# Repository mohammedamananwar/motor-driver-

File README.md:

# PCB 3D View

This is a 3D view of the designed PCB board.  
It contains various components such as:
- Terminal blocks for external connections (green connectors)
- IC (integrated circuit) mounted in DIP package
- Voltage regulator or transistor in TO-220 package with a heatsink
- A resistor
- A push button (yellow colored)
- Other essential electronic components required for circuit operation.

> **Note:**  
> There is a warning:  
> "**Board outline is missing or malformed. Run DRC for a full analysis.**"  
> Make sure to correct the board outline in your PCB design tool.

---

## 3D View Image:

---

## Observations:
- Proper placement of components is visible.
- Sufficient spacing for terminal connections.
- The IC and voltage regulator are well-positioned.
- Board outline needs to be corrected for final production.

## Suggestions:
- Fix the board outline error.
- Verify clearances and perform a Design Rule Check (DRC).
- Add labels for terminals (optional but helpful).

---

_Rendering Time:_ **16.663 seconds**

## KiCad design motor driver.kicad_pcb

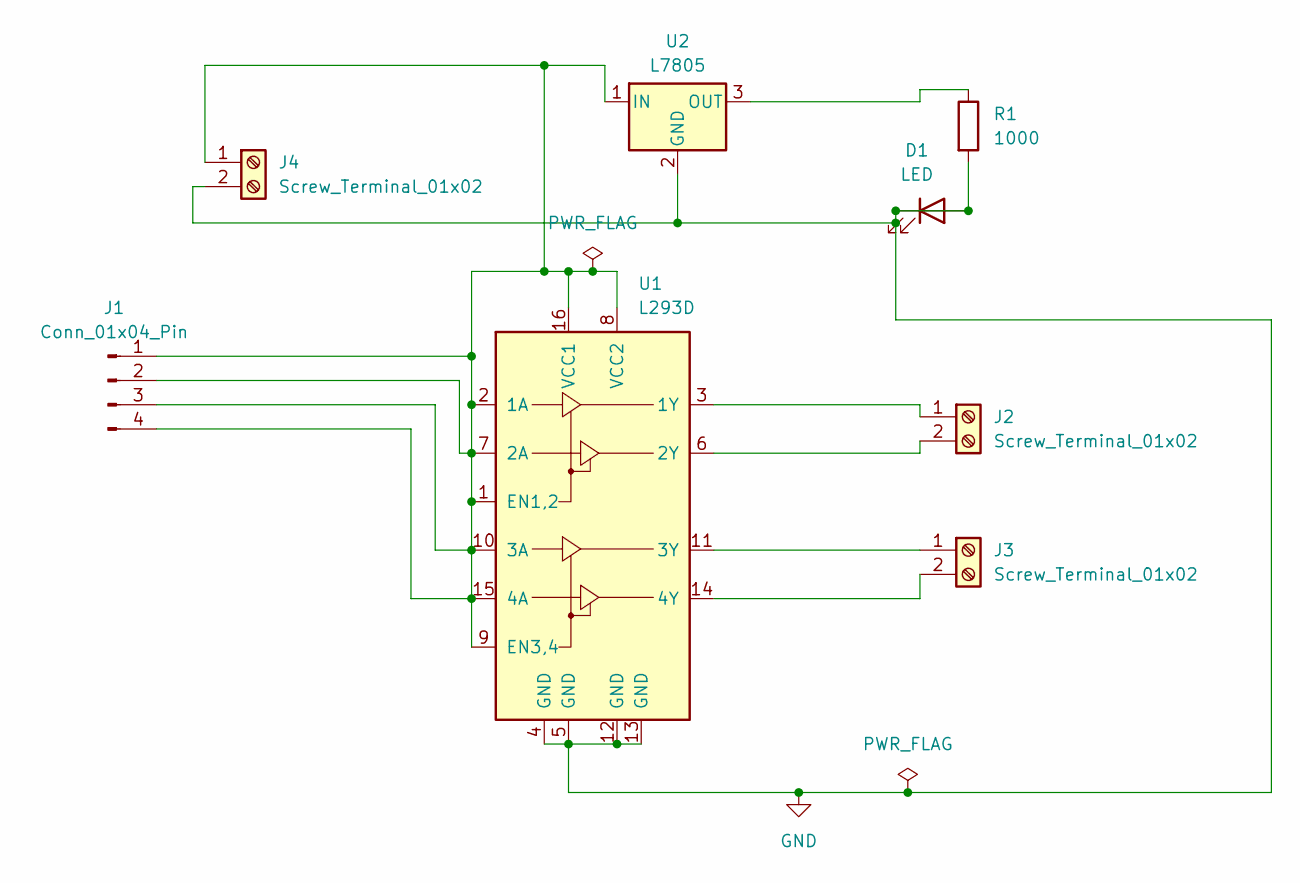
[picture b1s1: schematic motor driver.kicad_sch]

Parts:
D1: LED; LED_VCCLite_5381H7_6.35x6.35mm
J1: Conn_01x04_Pin; Molex_KK-254_AE-6410-04A_1x04_P2.54mm_Vertical
J2, J3, J4: Screw_Terminal_01x02; TerminalBlock_Phoenix_MKDS-1,5-2_1x02_P5.00mm_Horizontal
R1: 1000; R_Axial_DIN0207_L6.3mm_D2.5mm_P15.24mm_Horizontal
U1: L293D; DIP-16_W7.62mm
U2: L7805; TO-252-3_TabPin2

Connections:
GND: D1.1 (K), D1.2 (A), J4.2, R1.2, U1.4 (GND), U1.5 (GND), U1.12 (GND), U1.13 (GND), U2.2 (GND)
unnamed: J1.1, J1.2, J1.3, J1.4, J4.1, U1.1 (EN1,2), U1.2 (1A), U1.7 (2A), U1.8 (VCC2), U1.9 (EN3,4), U1.10 (3A), U1.15 (4A), U1.16 (VCC1), U2.1 (IN)
unnamed: J2.1, U1.3 (1Y)
unnamed: J2.2, U1.6 (2Y)
unnamed: J3.1, U1.11 (3Y)
unnamed: J3.2, U1.14 (4Y)
unnamed: R1.1, U2.3 (OUT)

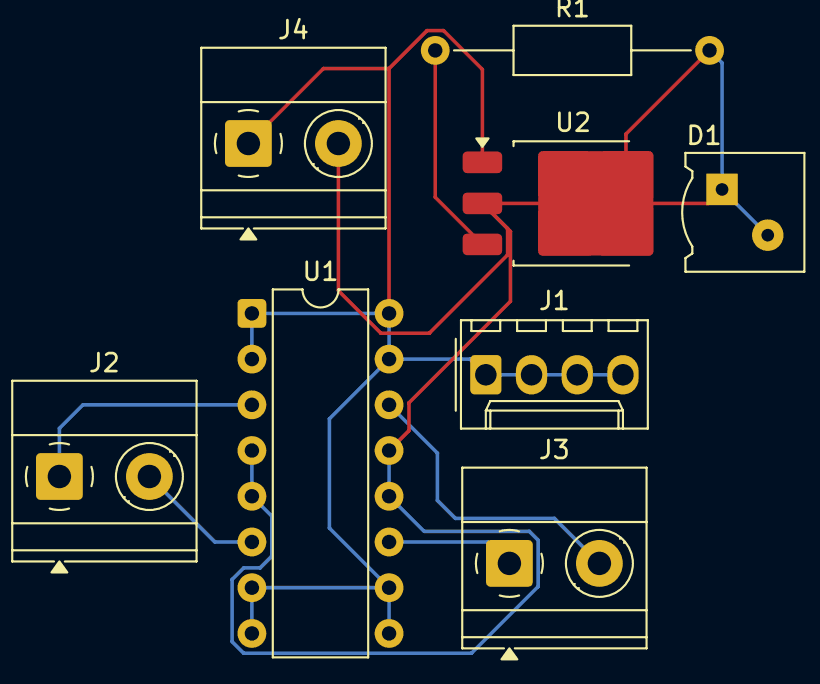
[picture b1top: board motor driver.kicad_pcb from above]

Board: 2 copper layers, 8 parts (0 on the bottom side), 7 nets.

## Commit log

2025-04-28 initial setup
2025-04-28 i have connected
2025-04-28 all file
2025-04-28 done
